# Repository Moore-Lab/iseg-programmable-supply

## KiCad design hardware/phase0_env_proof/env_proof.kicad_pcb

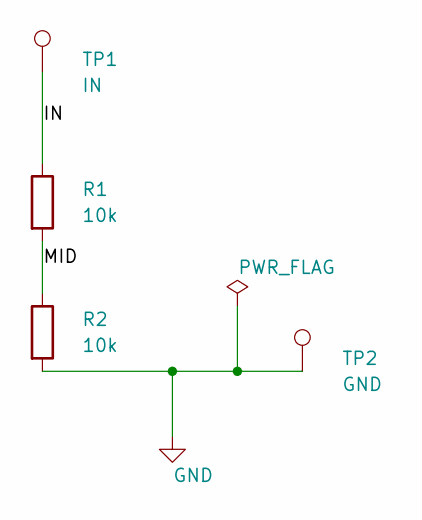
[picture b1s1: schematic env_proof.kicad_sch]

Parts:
R1, R2: 10k; R_0805_2012Metric
TP1: IN; TestPoint_Pad_D1.5mm
TP2: GND; TestPoint_Pad_D1.5mm

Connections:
/IN: R1.1, TP1.1
/MID: R1.2, R2.1
GND: R2.2, TP2.1

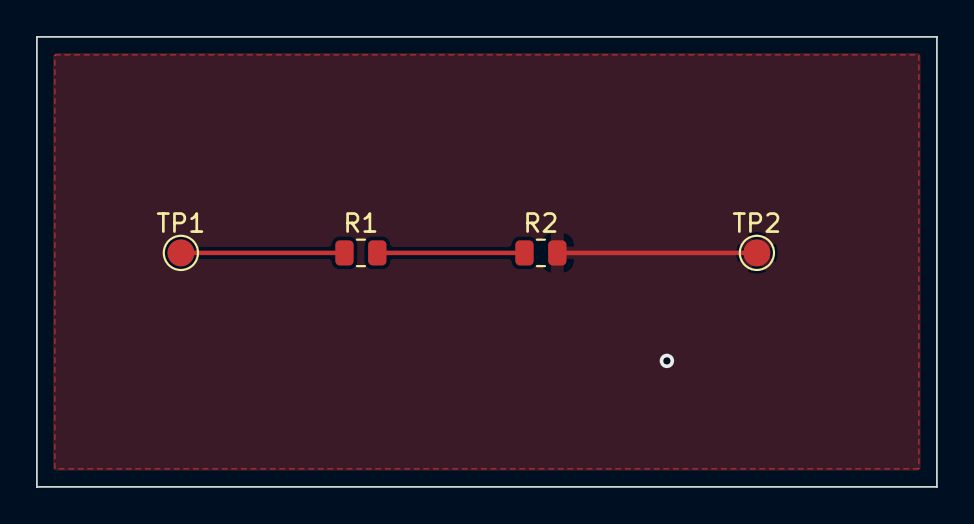
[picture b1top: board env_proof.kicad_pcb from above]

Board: 2 copper layers, 50.0 x 25.0 mm, 4 parts (0 on the bottom side), 3 nets.
